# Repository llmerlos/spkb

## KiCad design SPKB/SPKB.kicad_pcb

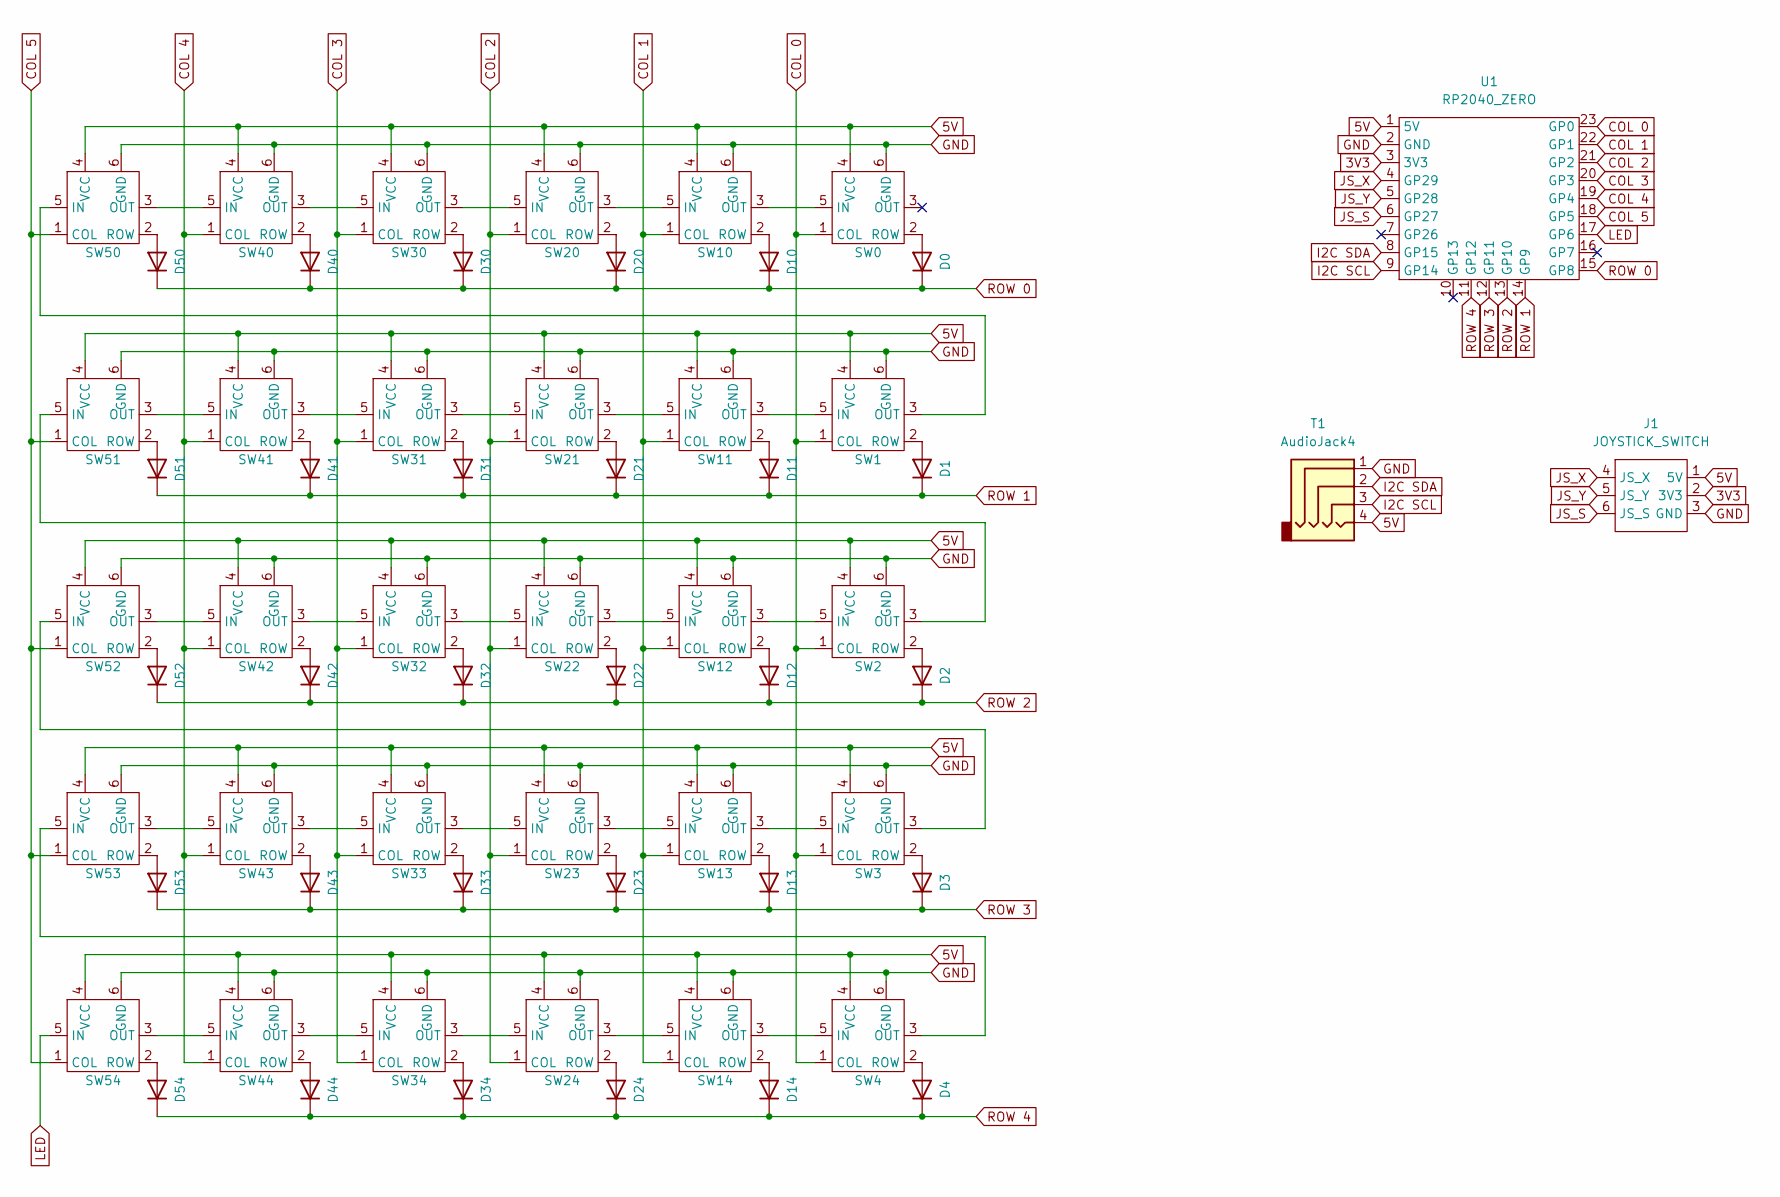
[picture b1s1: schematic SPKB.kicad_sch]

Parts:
D0, D1, D2, D3, D4, D10, D11, D12, D13, D14, D20, D21, D22, D23, D24, D30, D31, D32, D33, D34, D40, D41, D42, D43, D44, D50, D51, D52, D53, D54: 1N4148; D_DO-35_SOD27_P7.62mm_Horizontal
J1: JOYSTICK_SWITCH
SW0, SW1, SW2, SW3, SW4, SW10, SW11, SW12, SW13, SW14, SW20, SW21, SW22, SW23, SW24, SW30, SW31, SW32, SW33, SW34, SW40, SW41, SW42, SW43, SW44, SW50, SW51, SW52, SW53, SW54: SW_Push; Kailh_socket_PG1350_reversible_LED
T1: AudioJack4; TRRS-PJ-320A-dual
U1: RP2040_ZERO

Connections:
3V3: J1.2 (3V3), U1.3 (3V3)
5V: J1.1 (5V), SW0.4 (VCC), SW1.4 (VCC), SW2.4 (VCC), SW3.4 (VCC), SW4.4 (VCC), SW10.4 (VCC), SW11.4 (VCC), SW12.4 (VCC), SW13.4 (VCC), SW14.4 (VCC), SW20.4 (VCC), SW21.4 (VCC), SW22.4 (VCC), SW23.4 (VCC), SW24.4 (VCC), SW30.4 (VCC), SW31.4 (VCC), SW32.4 (VCC), SW33.4 (VCC), SW34.4 (VCC), SW40.4 (VCC), SW41.4 (VCC), SW42.4 (VCC), SW43.4 (VCC), SW44.4 (VCC), SW50.4 (VCC), SW51.4 (VCC), SW52.4 (VCC), SW53.4 (VCC), SW54.4 (VCC), T1.4, U1.1 (5V)
COL 0: SW0.1 (COL), SW1.1 (COL), SW2.1 (COL), SW3.1 (COL), SW4.1 (COL), U1.23 (GP0)
COL 1: SW10.1 (COL), SW11.1 (COL), SW12.1 (COL), SW13.1 (COL), SW14.1 (COL), U1.22 (GP1)
COL 2: SW20.1 (COL), SW21.1 (COL), SW22.1 (COL), SW23.1 (COL), SW24.1 (COL), U1.21 (GP2)
COL 3: SW30.1 (COL), SW31.1 (COL), SW32.1 (COL), SW33.1 (COL), SW34.1 (COL), U1.20 (GP3)
COL 4: SW40.1 (COL), SW41.1 (COL), SW42.1 (COL), SW43.1 (COL), SW44.1 (COL), U1.19 (GP4)
COL 5: SW50.1 (COL), SW51.1 (COL), SW52.1 (COL), SW53.1 (COL), SW54.1 (COL), U1.18 (GP5)
GND: J1.3 (GND), SW0.6 (GND), SW1.6 (GND), SW2.6 (GND), SW3.6 (GND), SW4.6 (GND), SW10.6 (GND), SW11.6 (GND), SW12.6 (GND), SW13.6 (GND), SW14.6 (GND), SW20.6 (GND), SW21.6 (GND), SW22.6 (GND), SW23.6 (GND), SW24.6 (GND), SW30.6 (GND), SW31.6 (GND), SW32.6 (GND), SW33.6 (GND), SW34.6 (GND), SW40.6 (GND), SW41.6 (GND), SW42.6 (GND), SW43.6 (GND), SW44.6 (GND), SW50.6 (GND), SW51.6 (GND), SW52.6 (GND), SW53.6 (GND), SW54.6 (GND), T1.1, U1.2 (GND)
I2C SCL: T1.3, U1.9 (GP14)
I2C SDA: T1.2, U1.8 (GP15)
JS_S: J1.6 (JS_S), U1.6 (GP27)
JS_X: J1.4 (JS_X), U1.4 (GP29)
JS_Y: J1.5 (JS_Y), U1.5 (GP28)
LED: SW54.5 (IN), U1.17 (GP6)
unnamed: D0.2 (A), SW0.2 (ROW)
unnamed: D1.2 (A), SW1.2 (ROW)
unnamed: D2.2 (A), SW2.2 (ROW)
unnamed: D3.2 (A), SW3.2 (ROW)
unnamed: D4.2 (A), SW4.2 (ROW)
unnamed: D10.2 (A), SW10.2 (ROW)
unnamed: D11.2 (A), SW11.2 (ROW)
unnamed: D12.2 (A), SW12.2 (ROW)
unnamed: D13.2 (A), SW13.2 (ROW)
unnamed: D14.2 (A), SW14.2 (ROW)
unnamed: D20.2 (A), SW20.2 (ROW)
unnamed: D21.2 (A), SW21.2 (ROW)
unnamed: D22.2 (A), SW22.2 (ROW)
unnamed: D23.2 (A), SW23.2 (ROW)
unnamed: D24.2 (A), SW24.2 (ROW)
unnamed: D30.2 (A), SW30.2 (ROW)
unnamed: D31.2 (A), SW31.2 (ROW)
unnamed: D32.2 (A), SW32.2 (ROW)
unnamed: D33.2 (A), SW33.2 (ROW)
unnamed: D34.2 (A), SW34.2 (ROW)
unnamed: D40.2 (A), SW40.2 (ROW)
unnamed: D41.2 (A), SW41.2 (ROW)
unnamed: D42.2 (A), SW42.2 (ROW)
unnamed: D43.2 (A), SW43.2 (ROW)
unnamed: D44.2 (A), SW44.2 (ROW)
unnamed: D50.2 (A), SW50.2 (ROW)
unnamed: D51.2 (A), SW51.2 (ROW)
unnamed: D52.2 (A), SW52.2 (ROW)
unnamed: D53.2 (A), SW53.2 (ROW)
unnamed: D54.2 (A), SW54.2 (ROW)
unnamed: SW0.5 (IN), SW10.3 (OUT)
unnamed: SW1.3 (OUT), SW50.5 (IN)
unnamed: SW1.5 (IN), SW11.3 (OUT)
unnamed: SW2.3 (OUT), SW51.5 (IN)
unnamed: SW3.3 (OUT), SW52.5 (IN)
unnamed: SW4.3 (OUT), SW53.5 (IN)
unnamed: SW10.5 (IN), SW20.3 (OUT)
unnamed: SW11.5 (IN), SW21.3 (OUT)
unnamed: SW2.5 (IN), SW12.3 (OUT)
unnamed: SW12.5 (IN), SW22.3 (OUT)
unnamed: SW3.5 (IN), SW13.3 (OUT)
unnamed: SW13.5 (IN), SW23.3 (OUT)
unnamed: SW4.5 (IN), SW14.3 (OUT)
unnamed: SW14.5 (IN), SW24.3 (OUT)
unnamed: SW20.5 (IN), SW30.3 (OUT)
unnamed: SW21.5 (IN), SW31.3 (OUT)
unnamed: SW22.5 (IN), SW32.3 (OUT)
unnamed: SW23.5 (IN), SW33.3 (OUT)
unnamed: SW24.5 (IN), SW34.3 (OUT)
unnamed: SW30.5 (IN), SW40.3 (OUT)
unnamed: SW31.5 (IN), SW41.3 (OUT)
unnamed: SW32.5 (IN), SW42.3 (OUT)
unnamed: SW33.5 (IN), SW43.3 (OUT)
unnamed: SW34.5 (IN), SW44.3 (OUT)
unnamed: SW40.5 (IN), SW50.3 (OUT)
unnamed: SW41.5 (IN), SW51.3 (OUT)
unnamed: SW42.5 (IN), SW52.3 (OUT)
unnamed: SW43.5 (IN), SW53.3 (OUT)
unnamed: SW44.5 (IN), SW54.3 (OUT)
ROW 0: D0.1 (K), D10.1 (K), D20.1 (K), D30.1 (K), D40.1 (K), D50.1 (K), U1.15 (GP8)
ROW 1: D1.1 (K), D11.1 (K), D21.1 (K), D31.1 (K), D41.1 (K), D51.1 (K), U1.14 (GP9)
ROW 2: D2.1 (K), D12.1 (K), D22.1 (K), D32.1 (K), D42.1 (K), D52.1 (K), U1.13 (GP10)
ROW 3: D3.1 (K), D13.1 (K), D23.1 (K), D33.1 (K), D43.1 (K), D53.1 (K), U1.12 (GP11)
ROW 4: D4.1 (K), D14.1 (K), D24.1 (K), D34.1 (K), D44.1 (K), D54.1 (K), U1.11 (GP12)

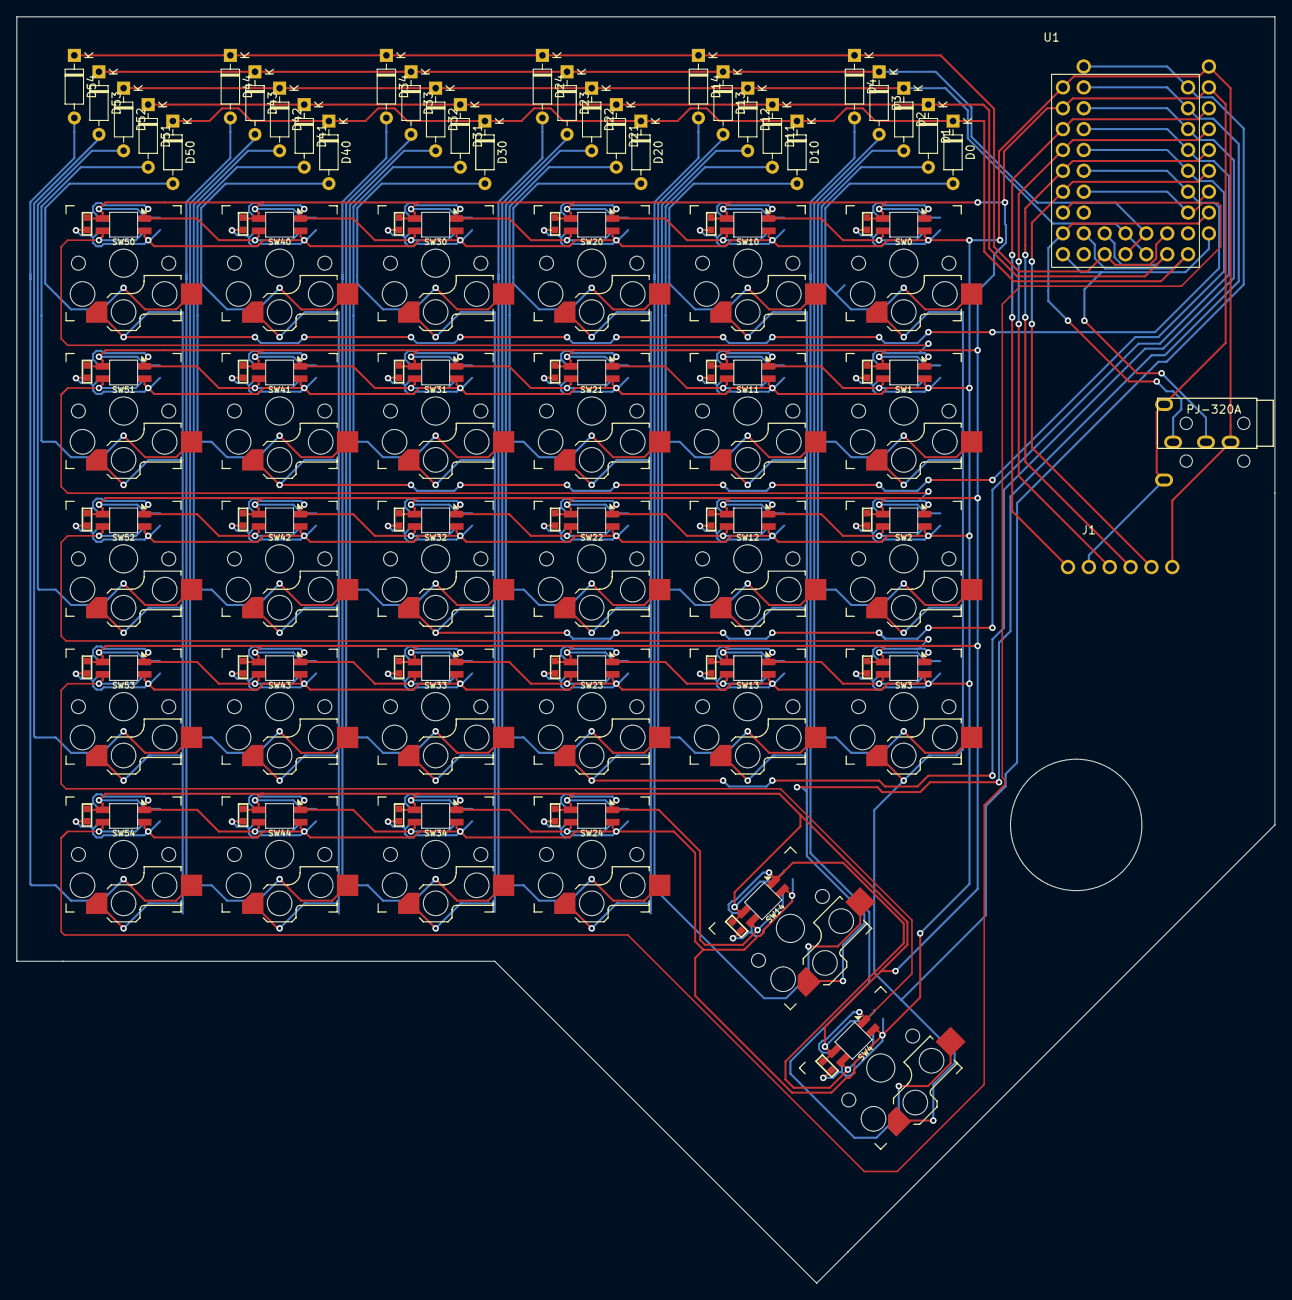
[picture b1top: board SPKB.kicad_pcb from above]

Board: 2 copper layers, 153.2 x 154.2 mm, 63 parts (0 on the bottom side), 79 nets.

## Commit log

2022-01-05 cleanup
2022-01-20 Work in progress
2022-01-20 cleanup discarded component
2022-01-27 PIO Matrix Scan
2022-01-27 handler implement
2022-01-27 LED functionality
2022-01-27 remove enum
2022-02-10 Keymap
2022-02-11 Keymap initial
2022-05-03 pico-sdk submodule
2022-05-03 FreeRTOS-Kernel smp submodule
2023-05-02 add pcb
